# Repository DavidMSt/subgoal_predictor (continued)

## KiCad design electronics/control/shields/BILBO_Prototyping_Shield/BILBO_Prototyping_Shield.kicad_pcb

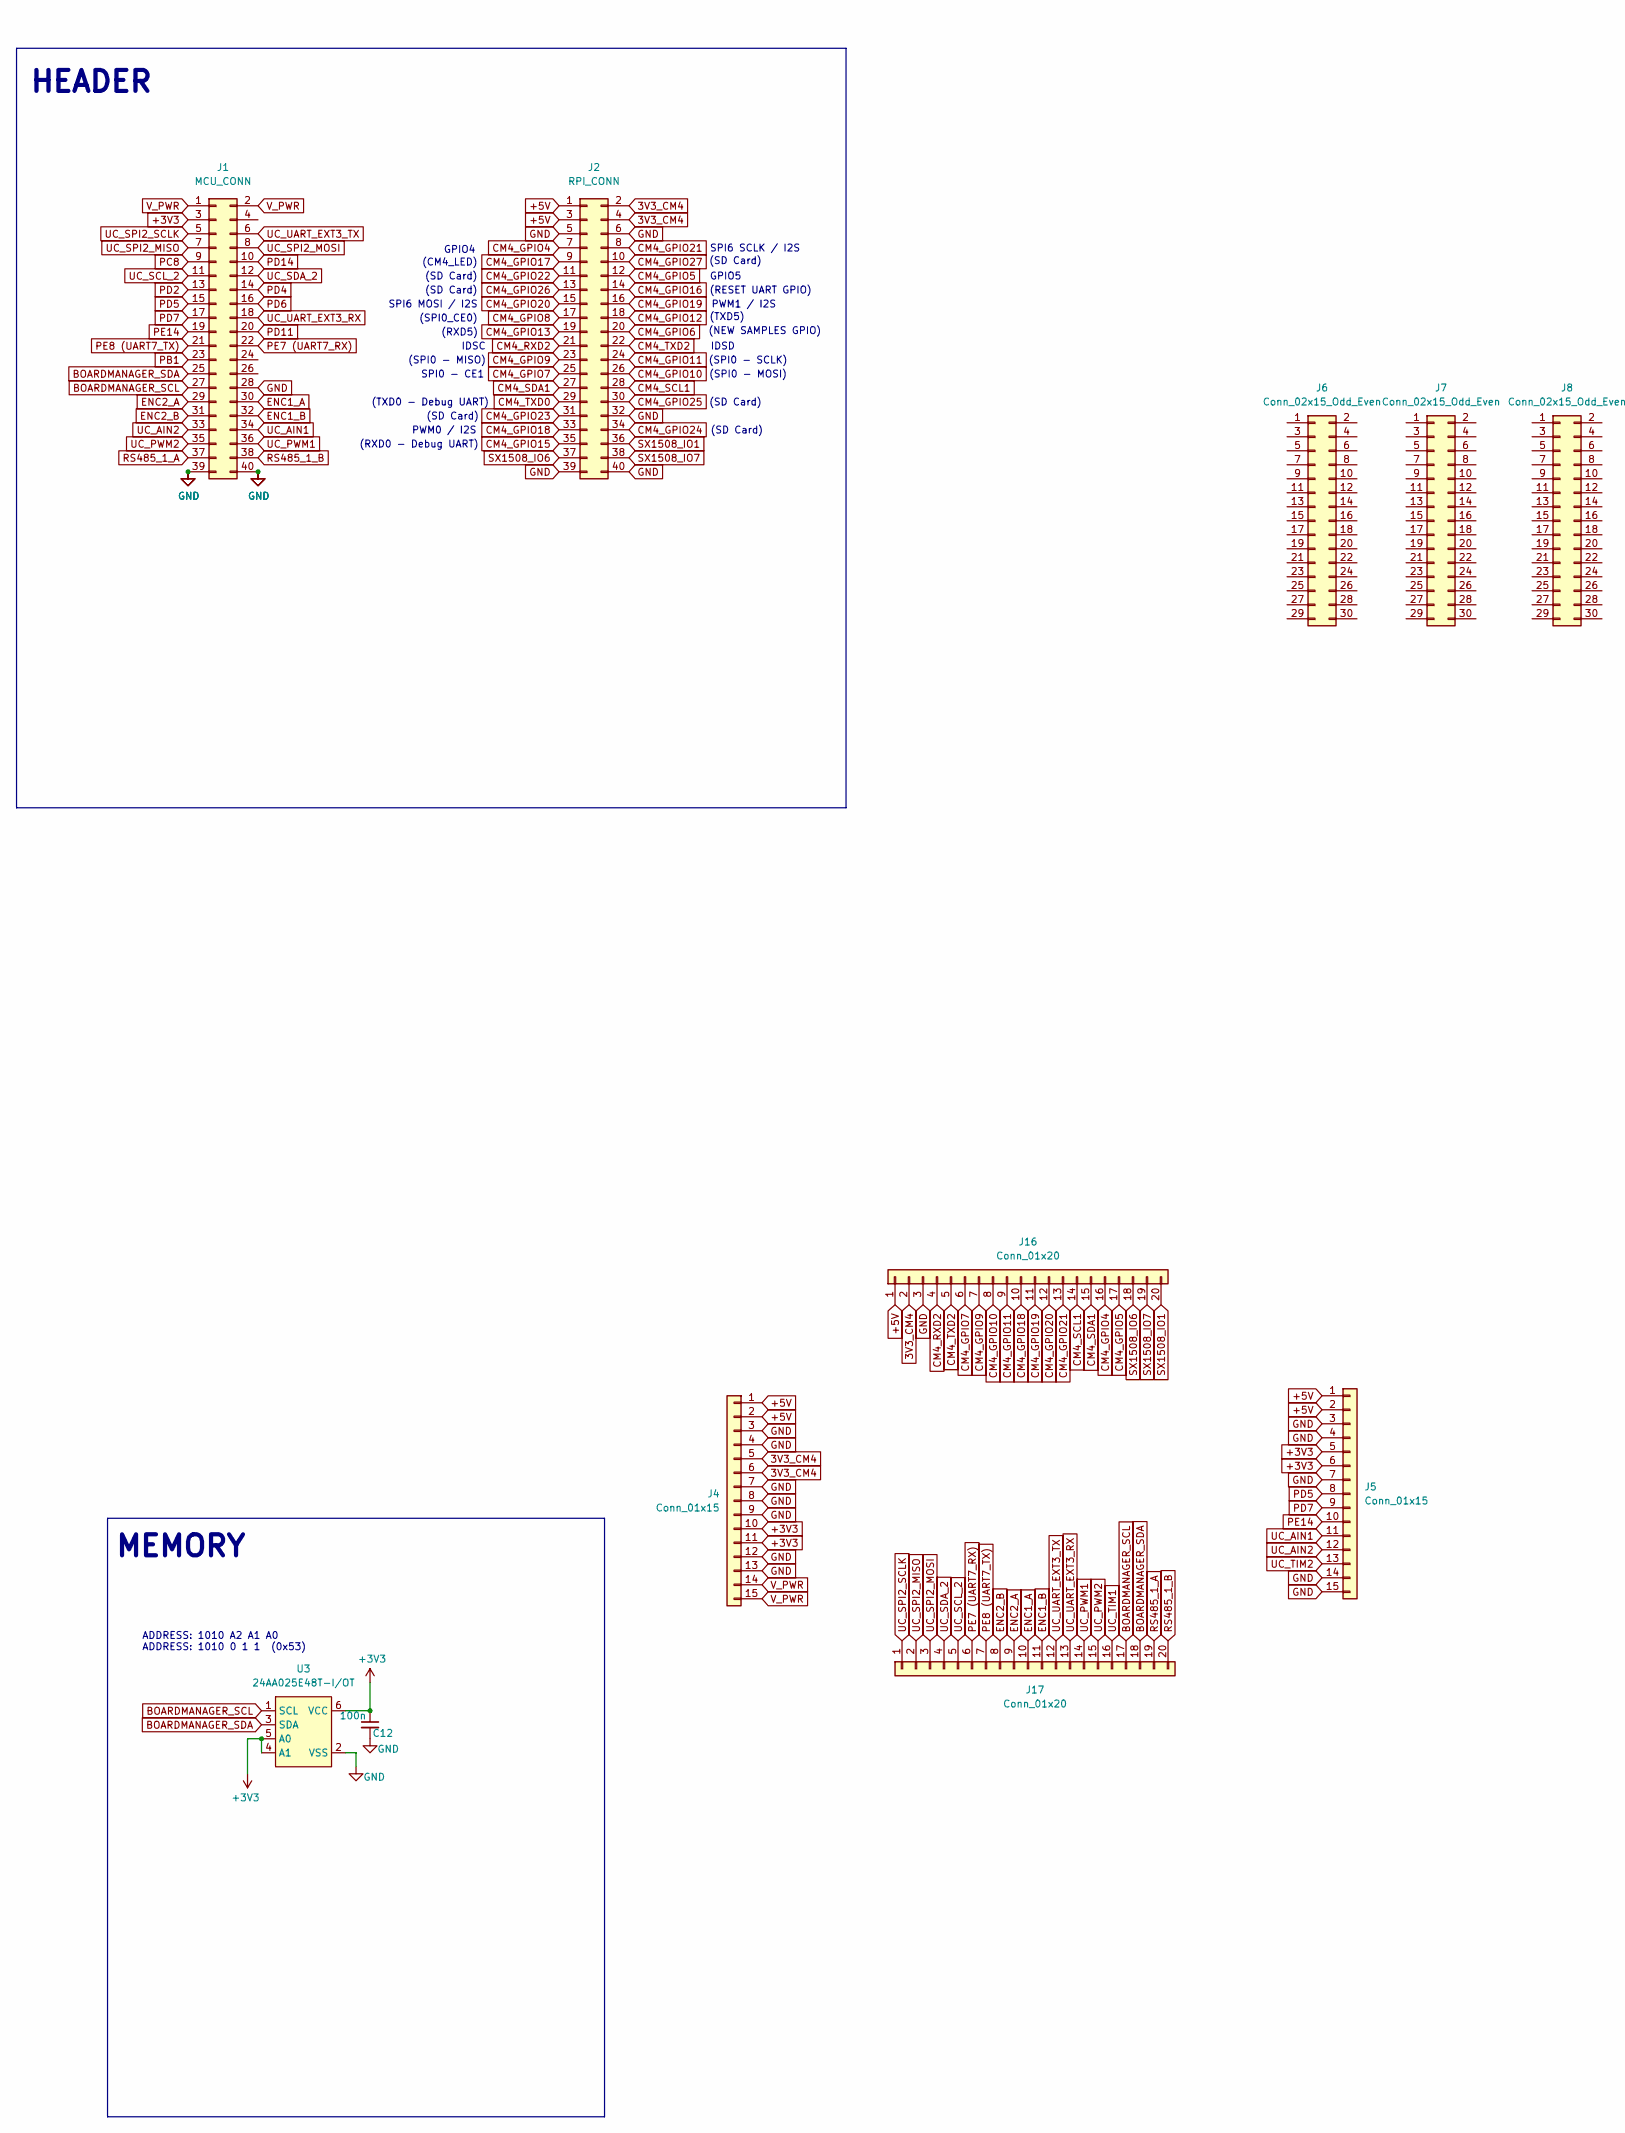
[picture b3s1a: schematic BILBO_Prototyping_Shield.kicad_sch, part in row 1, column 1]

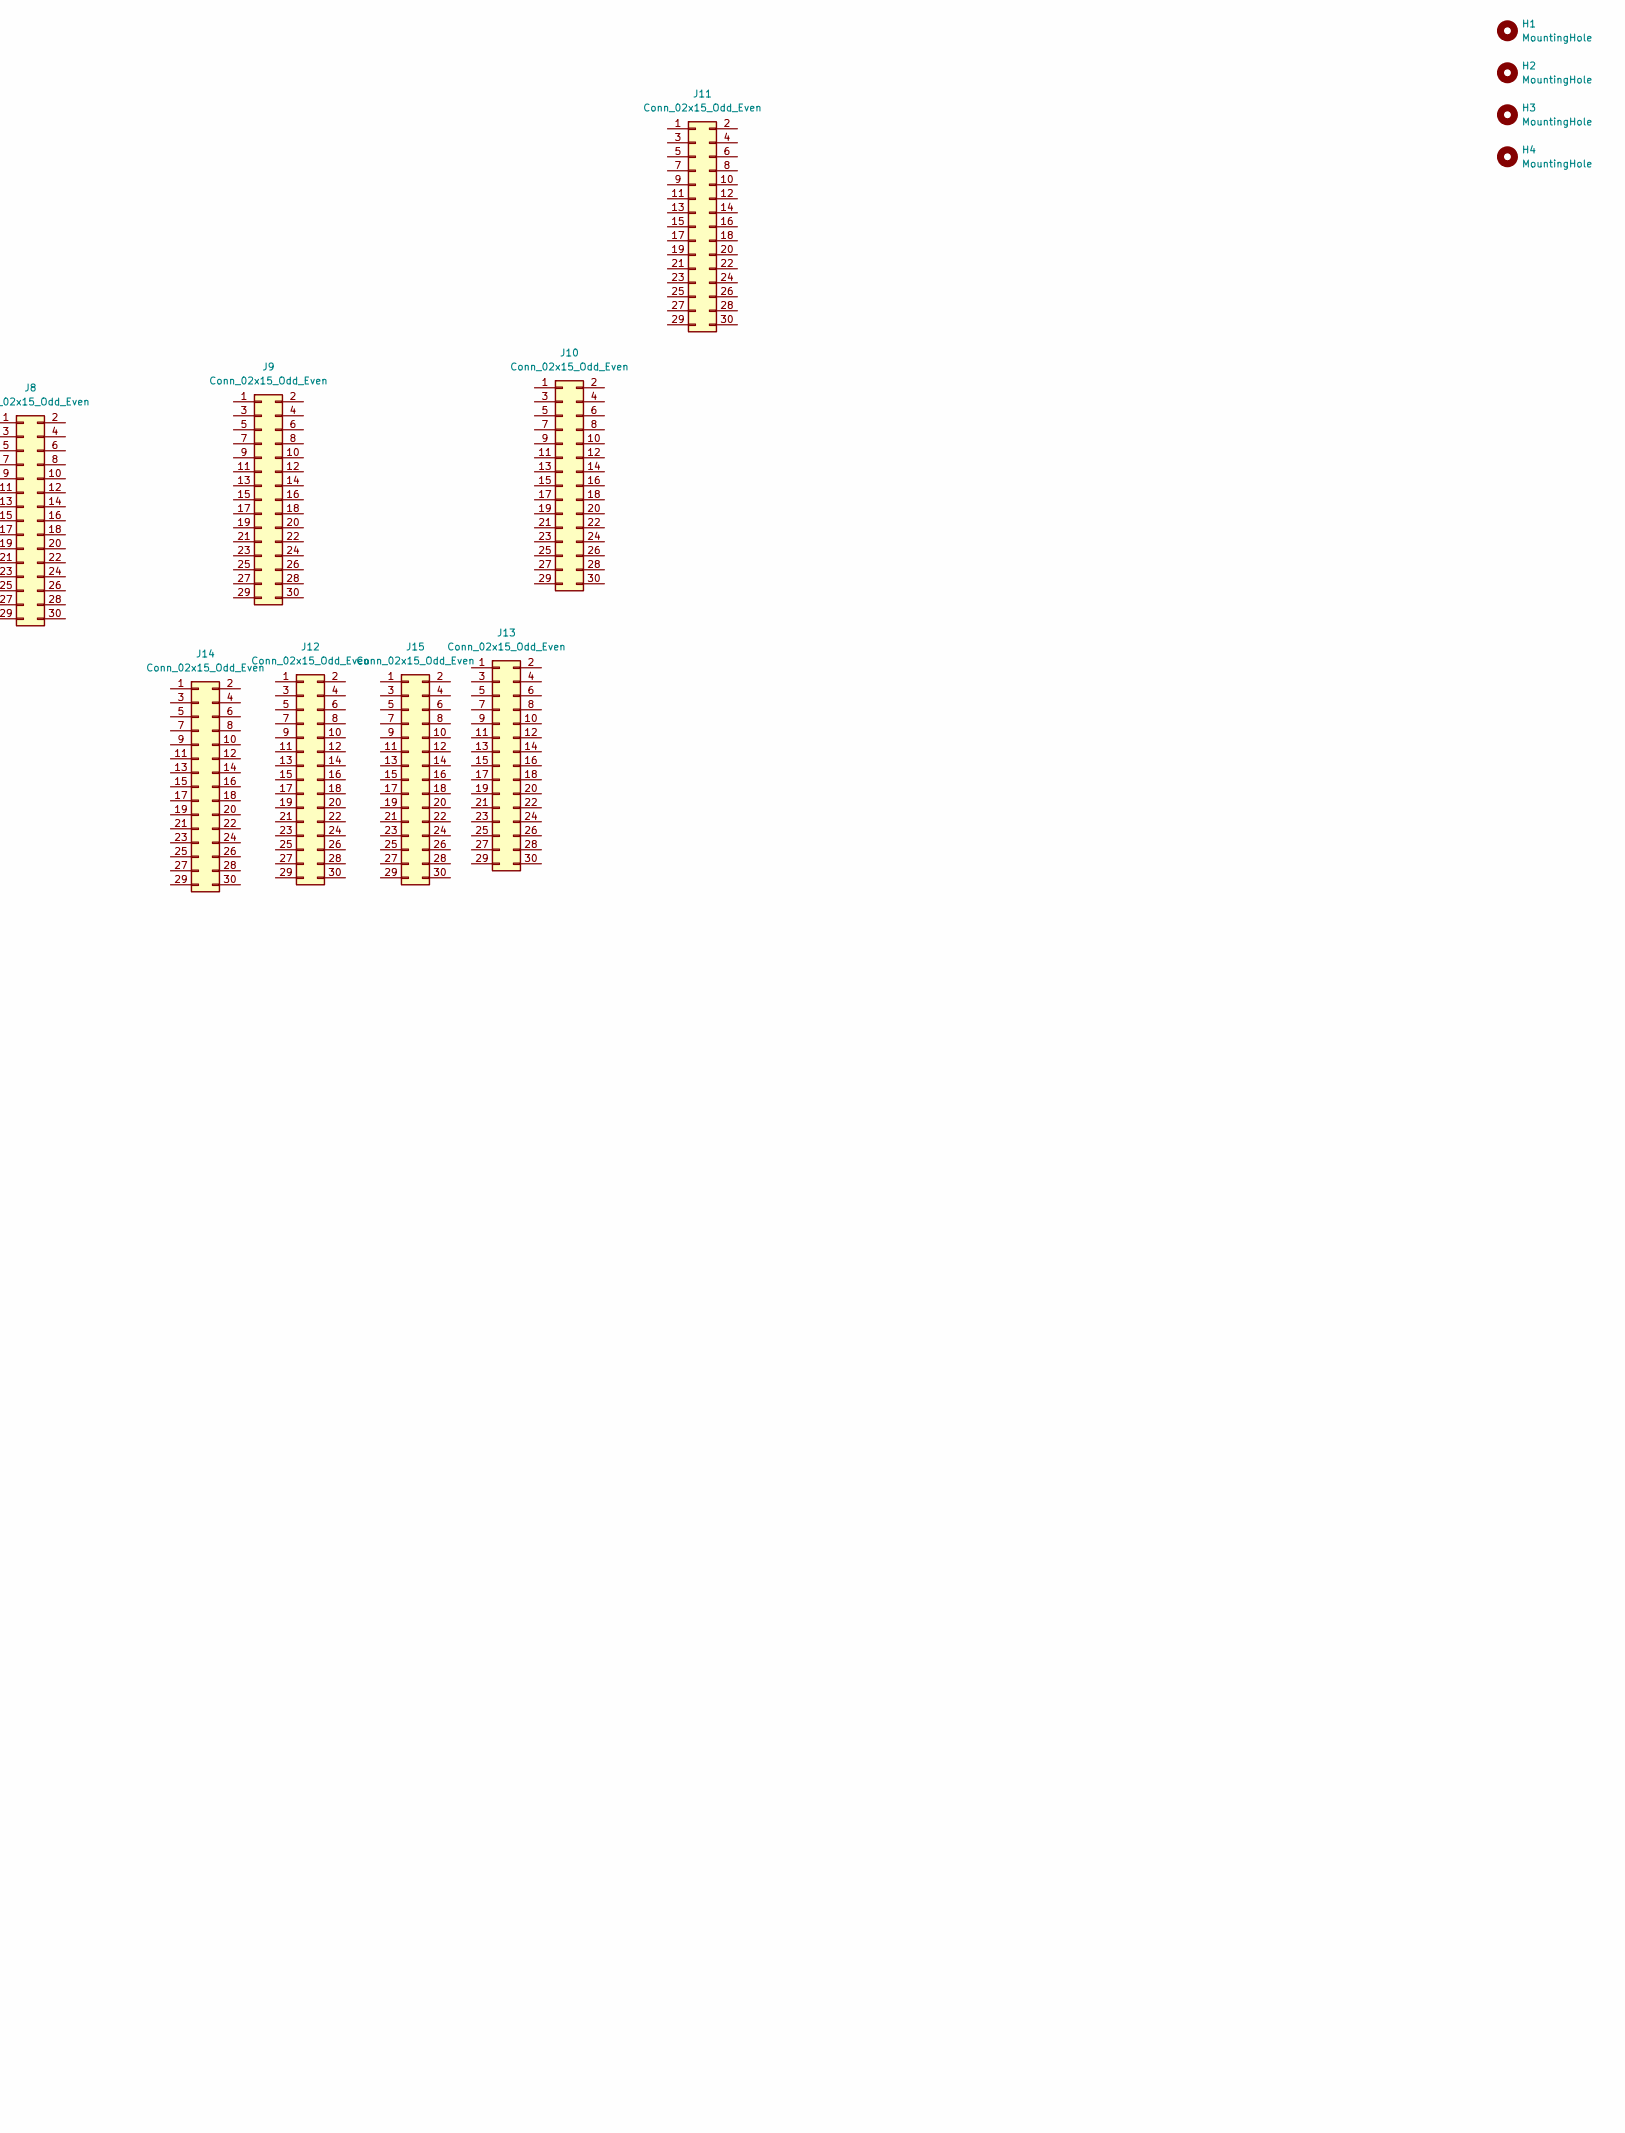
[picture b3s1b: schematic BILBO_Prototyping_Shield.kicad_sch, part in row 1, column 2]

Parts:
C12: 100n; C_0603_1608Metric
H1, H2, H3, H4: MountingHole; MountingHole_2.7mm_M2.5_DIN965
J1: MCU_CONN; PinHeader_2x20_P2.54mm_Vertical
J2: RPI_CONN; PinHeader_2x20_P2.54mm_Vertical
J4, J5: Conn_01x15; PinHeader_1x15_P2.54mm_Vertical
J6, J7, J8, J9, J10, J11, J12, J13, J14, J15: Conn_02x15_Odd_Even; PinHeader_2x15_P2.54mm_Vertical
J16, J17: Conn_01x20; PinHeader_1x20_P2.54mm_Vertical
U3: 24AA025E48T-I/OT; SOT-23-6_Handsoldering

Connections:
3V3_CM4: J2.2, J2.4, J4.5, J4.6, J16.2
+3V3: C12.1, J1.3, J4.10, J4.11, J5.5, J5.6, U3.4 (A1), U3.5 (A0), U3.6 (VCC)
+5V: J2.1, J2.3, J4.1, J4.2, J5.1, J5.2, J16.1
BOARDMANAGER_SCL: J1.27, J17.17, U3.1 (SCL)
BOARDMANAGER_SDA: J1.25, J17.18, U3.3 (SDA)
CM4_GPIO4: J2.7, J16.16
CM4_GPIO5: J2.12, J16.17
CM4_GPIO6: J2.20
CM4_GPIO7: J2.25, J16.6
CM4_GPIO8: J2.17
CM4_GPIO9: J2.23, J16.7
CM4_GPIO10: J2.26, J16.8
CM4_GPIO11: J2.24, J16.9
CM4_GPIO12: J2.18
CM4_GPIO13: J2.19
CM4_GPIO15: J2.35
CM4_GPIO16: J2.14
CM4_GPIO17: J2.9
CM4_GPIO18: J2.33, J16.10
CM4_GPIO19: J2.16, J16.11
CM4_GPIO20: J2.15, J16.12
CM4_GPIO21: J2.8, J16.13
CM4_GPIO22: J2.11
CM4_GPIO23: J2.31
CM4_GPIO24: J2.34
CM4_GPIO25: J2.30
CM4_GPIO26: J2.13
CM4_GPIO27: J2.10
CM4_RXD2: J2.21, J16.4
CM4_SCL1: J2.28, J16.14
CM4_SDA1: J2.27, J16.15
CM4_TXD0: J2.29
CM4_TXD2: J2.22, J16.5
ENC1_A: J1.30, J17.10
ENC1_B: J1.32, J17.11
ENC2_A: J1.29, J17.9
ENC2_B: J1.31, J17.8
GND: C12.2, J1.28, J1.39, J1.40, J2.5, J2.6, J2.32, J2.39, J2.40, J4.3, J4.4, J4.7, J4.8, J4.9, J4.12, J4.13, J5.3, J5.4, J5.7, J5.14, J5.15, J16.3, U3.2 (VSS)
PB1: J1.23
PC8: J1.9
PD2: J1.13
PD4: J1.14
PD5: J1.15, J5.8
PD6: J1.16
PD7: J1.17, J5.9
PD11: J1.20
PD14: J1.10
PE7 (UART7_RX): J1.22, J17.6
PE8 (UART7_TX): J1.21, J17.7
PE14: J1.19, J5.10
RS485_1_A: J1.37, J17.19
RS485_1_B: J1.38, J17.20
SX1508_IO1: J2.36, J16.20
SX1508_IO6: J2.37, J16.18
SX1508_IO7: J2.38, J16.19
UC_AIN1: J1.34, J5.11
UC_AIN2: J1.33, J5.12
UC_PWM1: J1.36, J17.14
UC_PWM2: J1.35, J17.15
UC_SCL_2: J1.11, J17.5
UC_SDA_2: J1.12, J17.4
UC_SPI2_MISO: J1.7, J17.2
UC_SPI2_MOSI: J1.8, J17.3
UC_SPI2_SCLK: J1.5, J17.1
UC_TIM1: J17.16
UC_TIM2: J5.13
UC_UART_EXT3_RX: J1.18, J17.13
UC_UART_EXT3_TX: J1.6, J17.12
V_PWR: J1.1, J1.2, J4.14, J4.15

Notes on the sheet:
(SD Card)
(NEW SAMPLES GPIO)
(TXD0 - Debug UART)
(SPI0 - SCLK)
PWM0 / I2S
(CM4_LED)
ADDRESS: 1010 A2 A1 A0 ADDRESS: 1010 0 1 1 (0x53)
IDSC
(SPI0_CE0)
(RESET UART GPIO)
(SPI0 - MOSI)
MEMORY
SPI6 SCLK / I2S
SPI6 MOSI / I2S
IDSD
GPIO4
(RXD0 - Debug UART)
HEADER
SPI0 - CE1
PWM1 / I2S
(TXD5)
(RXD5)
(SPI0 - MISO)
GPIO5

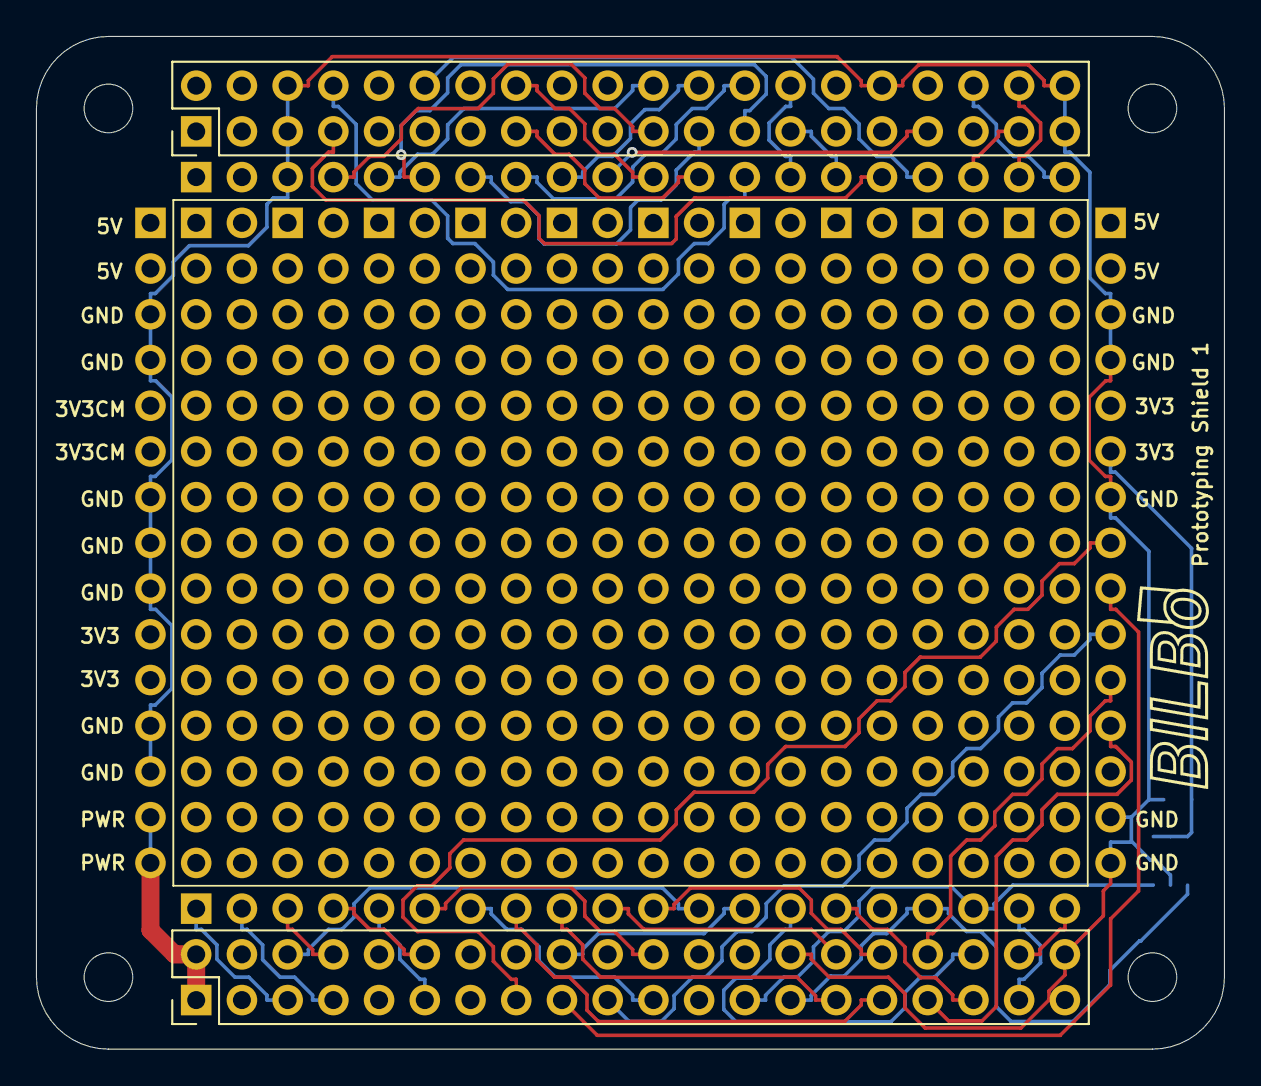
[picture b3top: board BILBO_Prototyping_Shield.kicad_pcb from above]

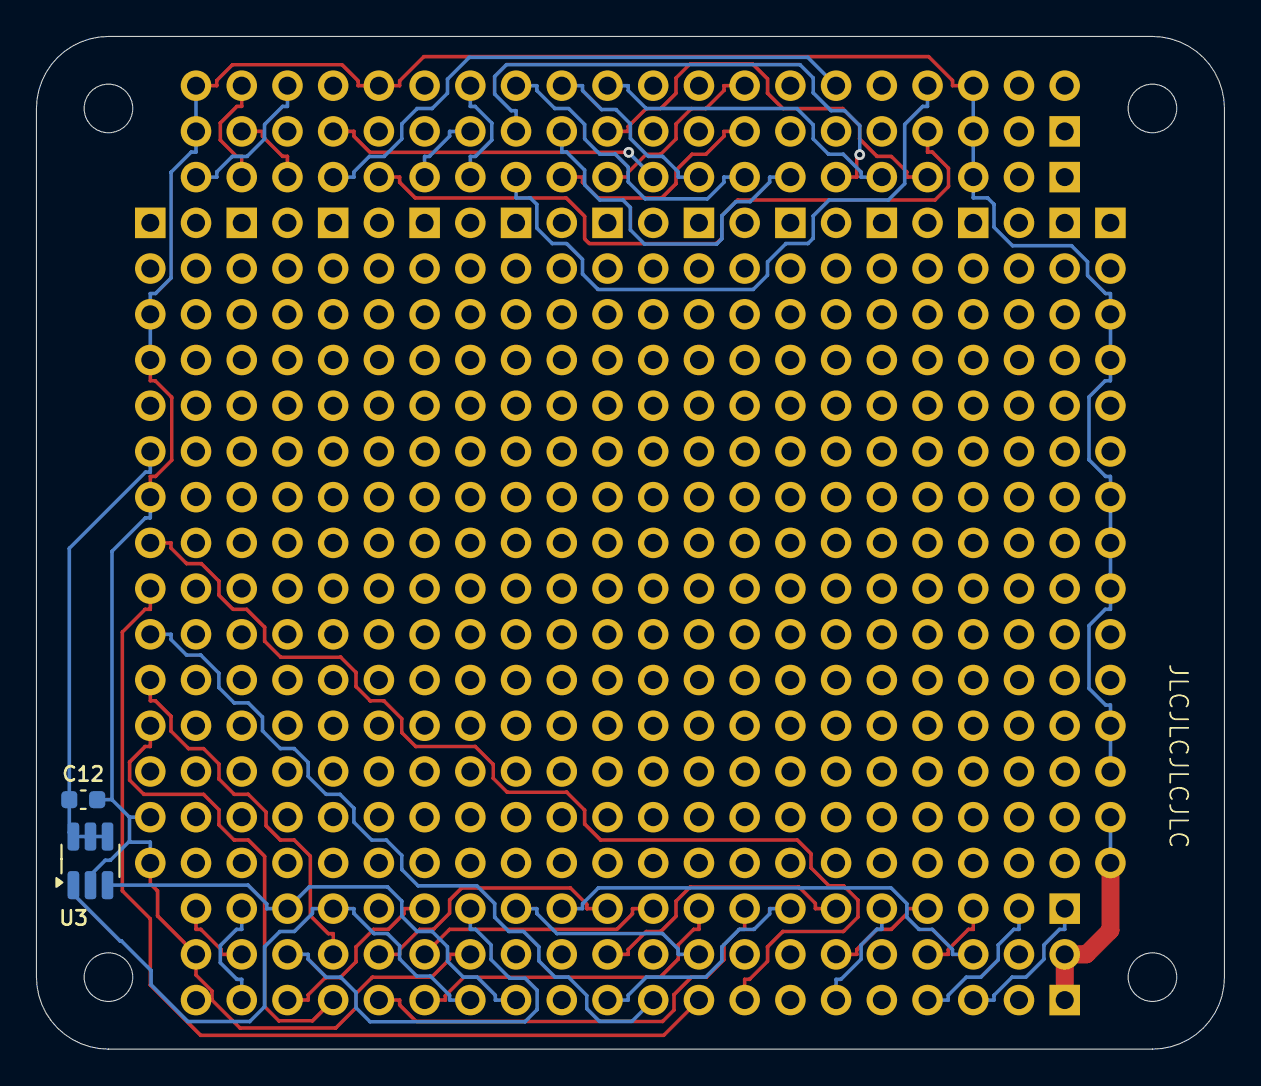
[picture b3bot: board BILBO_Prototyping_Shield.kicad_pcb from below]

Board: 4 copper layers, 66.0 x 56.3 mm, 22 parts (2 on the bottom side), 46 nets.

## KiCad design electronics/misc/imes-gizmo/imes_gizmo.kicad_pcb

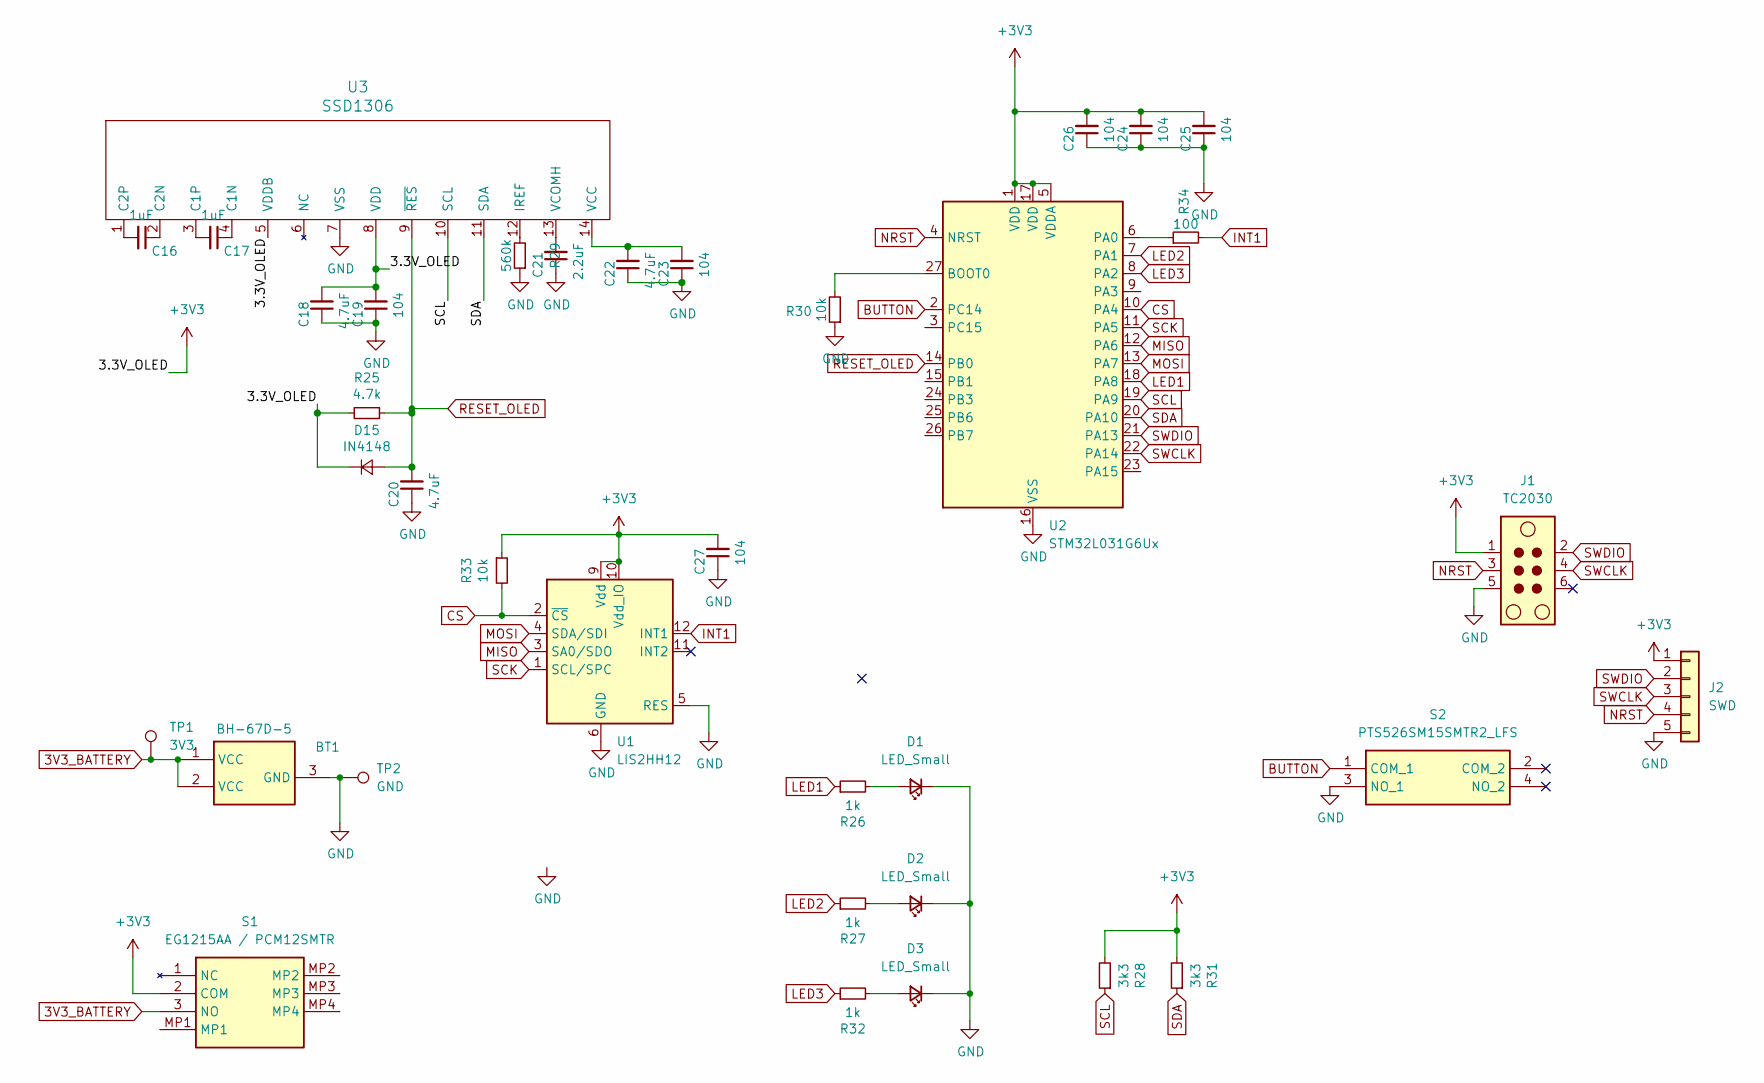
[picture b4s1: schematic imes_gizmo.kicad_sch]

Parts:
BT1: BH-67D-5; BH67D5; Manufacturer_Part_Number BH-67D-5; Mouser Part Number 737-BH-67D-5
C16, C17: 1uF; C_0805_2012Metric
C18, C20, C22: 4.7uF; C_0805_2012Metric
C19, C23, C24, C25, C26, C27: 104; C_0603_1608Metric
C21: 2.2uF; C_0805_2012Metric
D1, D2, D3: LED_Small; LED_0603_1608Metric
D15: IN4148; D_SOD-123
J1: TC2030; Tag-Connect_TC2030-IDC-NL_2x03_P1.27mm_Vertical
J2: SWD; M208900505
R25: 4.7k; R_0603_1608Metric
R26, R27, R32: 1k; R_0603_1608Metric
R28, R31: 3k3; R_0603_1608Metric
R29: 560k; R_0603_1608Metric
R30, R33: 10k; R_0603_1608Metric
R34: 100; R_0603_1608Metric
S1: EG1215AA / PCM12SMTR; EG1215AA; Manufacturer_Part_Number EG1215AA; Mouser Part Number 612-EG1215AA
S2: PTS526SM15SMTR2_LFS; PTS526SM15SMTR2LFS; Manufacturer_Part_Number PTS526SM15SMTR2 LFS; Mouser Part Number 611-PTS526SM15SMTR2L
TP1: 3V3; TestPoint_Pad_D3.0mm
TP2: GND; TestPoint_Pad_D3.0mm
U1: LIS2HH12; LGA-12_2x2mm_P0.5mm
U2: STM32L031G6Ux; QFN50P400X400X60-28N-D
U3: SSD1306; SSD1306_OLED-0.91-128x32

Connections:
3V3_BATTERY: BT1.1 (VCC), BT1.2 (VCC), S1.3 (NO), TP1.1
+3V3: C18.2, C19.2, C24.2, C25.2, C26.2, C27.2, D15.1 (K), J1.1, J2.1, R25.2, R28.2, R31.2, R33.1, S1.2 (COM), U1.9 (Vdd), U1.10 (Vdd_IO), U2.1 (VDD), U2.5 (VDDA), U2.17 (VDD), U3.5 (VDDB), U3.8 (VDD)
BUTTON: S2.1 (COM_1), U2.2 (PC14)
CS: R33.2, U1.2 (~CS), U2.10 (PA4)
GND: BT1.3 (GND), C18.1, C19.1, C20.1, C21.1, C22.1, C23.1, C24.1, C25.1, C26.1, C27.1, D1.1 (K), D2.1 (K), D3.1 (K), J1.5, J2.5, R29.1, R30.1, S2.3 (NO_1), TP2.1, U1.5 (RES), U1.6 (GND), U1.7 (GND), U1.8 (GND), U2.16 (VSS), U2.28 (VSS), U3.7 (VSS)
INT1: R34.2, U1.12 (INT1)
LED1: R26.1, U2.18 (PA8)
LED2: R27.1, U2.7 (PA1)
LED3: R32.1, U2.8 (PA2)
MISO: U1.3 (SA0/SDO), U2.12 (PA6)
MOSI: U1.4 (SDA/SDI), U2.13 (PA7)
NRST: J1.3, J2.4, U2.4 (NRST)
unnamed: D1.2 (A), R26.2
unnamed: D2.2 (A), R27.2
unnamed: D3.2 (A), R32.2
unnamed: R30.2, U2.27 (BOOT0)
unnamed: R34.1, U2.6 (PA0)
unnamed: C17.1, U3.4 (C1N)
unnamed: C17.2, U3.3 (C1P)
unnamed: C16.1, U3.2 (C2N)
unnamed: C16.2, U3.1 (C2P)
unnamed: R29.2, U3.12 (IREF)
unnamed: C22.2, C23.2, U3.14 (VCC)
unnamed: C21.2, U3.13 (VCOMH)
RESET_OLED: C20.2, D15.2 (A), R25.1, U2.14 (PB0), U3.9 (~RES)
SCK: U1.1 (SCL/SPC), U2.11 (PA5)
SCL: R28.1, U2.19 (PA9), U3.10 (SCL)
SDA: R31.1, U2.20 (PA10), U3.11 (SDA)
SWCLK: J1.4, J2.3, U2.22 (PA14)
SWDIO: J1.2, J2.2, U2.21 (PA13)

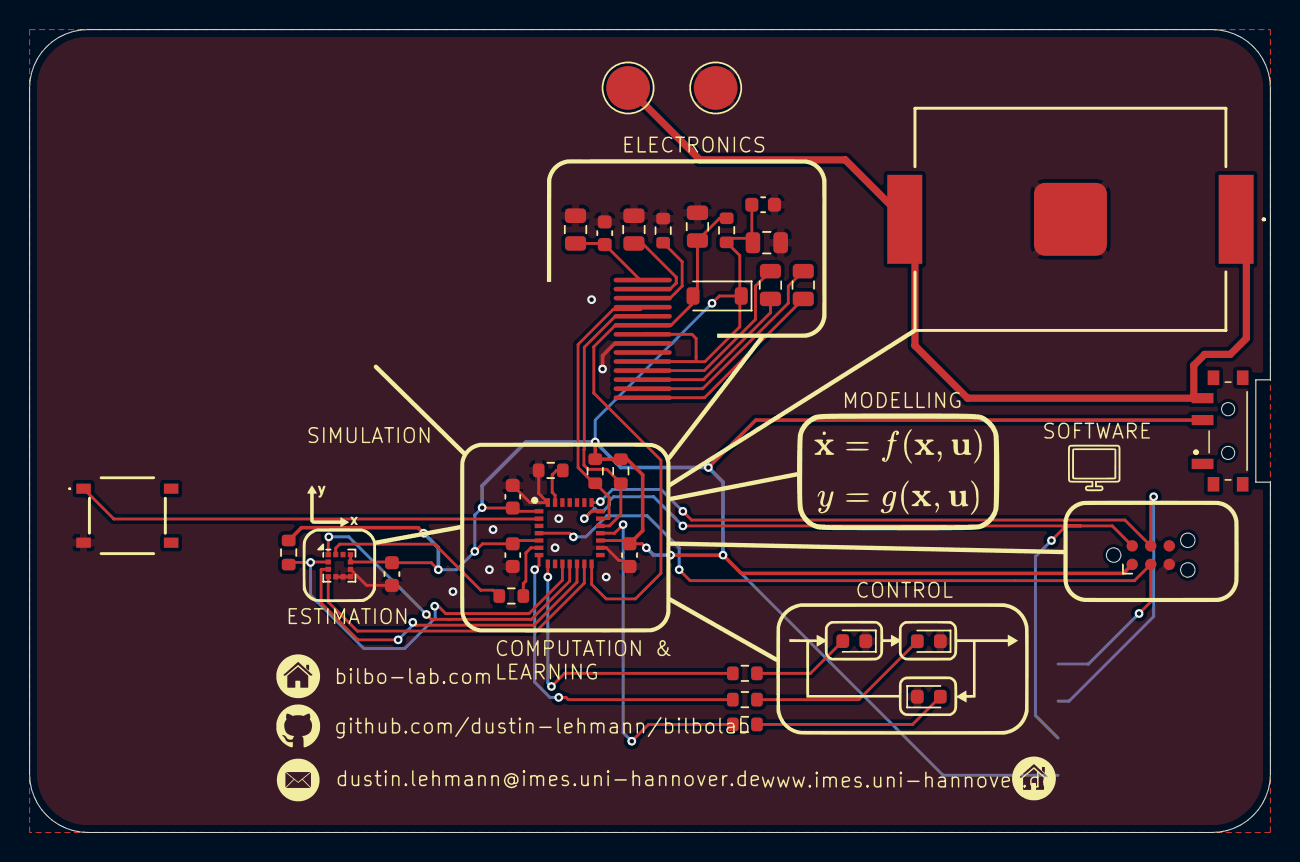
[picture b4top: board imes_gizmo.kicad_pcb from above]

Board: 2 copper layers, 85.0 x 55.0 mm, 36 parts (1 on the bottom side), 30 nets.

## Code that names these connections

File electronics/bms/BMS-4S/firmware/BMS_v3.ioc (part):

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Mcu.Name=STM32L432K(B-C)Ux
Mcu.Package=UFQFPN32
Mcu.UserName=STM32L432KBUx
PA0.Signal=ADCx_IN5
PA1.GPIOParameters=GPIO_Label
PA1.GPIO_Label=ENABLE_MEAS_1
PA1.Signal=GPIO_Output
PA10.Mode=I2C
PA10.Signal=I2C1_SDA
PA11.GPIOParameters=GPIO_Label
PA11.GPIO_Label=LED_USER
PA11.Signal=GPIO_Output
PA13\ (JTMS-SWDIO).Mode=Serial_Wire
PA13\ (JTMS-SWDIO).Signal=SYS_JTMS-SWDIO
PA14\ (JTCK-SWCLK).Mode=Serial_Wire
PA14\ (JTCK-SWCLK).Signal=SYS_JTCK-SWCLK
PA15\ (JTDI).Signal=GPIO_Analog
PA2.Signal=ADCx_IN7
PA4.Signal=ADCx_IN9
PA5.GPIOParameters=GPIO_Label
PA5.GPIO_Label=ENABLE_MEAS_3
PA5.Signal=GPIO_Output
PA6.GPIOParameters=GPIO_PuPd,GPIO_Label
PA6.GPIO_Label=DETECT_CHG
PA6.GPIO_PuPd=GPIO_PULLUP
PA6.Signal=GPIO_Input
PA7.Mode=I2C
PA7.Signal=I2C3_SCL
PA9.Mode=I2C
PA9.Signal=I2C1_SCL
PB0.Signal=ADCx_IN15
PB1.GPIOParameters=GPIO_Label
PB1.GPIO_Label=ENABLE_MEAS_4
PB1.Signal=GPIO_Output
PB3\ (JTDO-TRACESWO).GPIOParameters=GPIO_Label
PB3\ (JTDO-TRACESWO).GPIO_Label=OUT_2
PB3\ (JTDO-TRACESWO).Signal=GPIO_Output
PB4\ (NJTRST).Mode=I2C
PB4\ (NJTRST).Signal=I2C3_SDA
PB5.GPIOParameters=GPIO_Label
PB5.GPIO_Label=OUT_1
PB5.Signal=GPIO_Output
PB6.GPIOParameters=GPIO_Label
PB6.GPIO_Label=OUT_3
PB6.Signal=GPIO_Output
PB7.GPIOParameters=GPIO_Label
PB7.GPIO_Label=OUT_4
PB7.Signal=GPIO_Output
RCC.HSE_VALUE=8000000
RCC.SYSCLKFreq_VALUE=16000000
RCC.SYSCLKSource=RCC_SYSCLKSOURCE_HSI
board=custom

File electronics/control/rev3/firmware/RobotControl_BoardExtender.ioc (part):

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Mcu.Name=STM32G031G(4-6-8)Ux
Mcu.Package=UFQFPN28
Mcu.UserName=STM32G031G8Ux
PA0.Mode=IN0
PA0.Signal=ADC1_IN0
PA1.Mode=IN1
PA1.Signal=ADC1_IN1
PA11\ [PA9].Mode=I2C
PA11\ [PA9].Signal=I2C2_SCL
PA12\ [PA10].Mode=I2C
PA12\ [PA10].Signal=I2C2_SDA
PA13.Mode=Serial_Wire
PA13.Signal=SYS_SWDIO
PA14-BOOT0.Mode=Serial_Wire
PA14-BOOT0.Signal=SYS_SWCLK
PA15.GPIOParameters=GPIO_Label
PA15.GPIO_Label=LED
PA15.Signal=GPIO_Output
PA2.GPIOParameters=GPIO_Label
PA2.GPIO_Label=ENABLE_SD
PA2.Signal=GPIO_Output
PA3.Mode=IN3
PA3.Signal=ADC1_IN3
PA4.GPIOParameters=GPIO_Label
PA4.GPIO_Label=DETECT_SD
PA4.Signal=GPIO_Input
PA5.GPIOParameters=GPIO_PuPd
PA5.GPIO_PuPd=GPIO_PULLDOWN
PA5.Signal=S_TIM2_CH1_ETR
PA6.GPIOParameters=GPIO_PuPd,GPIO_Label
PA6.GPIO_Label=DETECT_USB
PA6.GPIO_PuPd=GPIO_PULLUP
PA6.Signal=GPIO_Input
PA8.GPIOParameters=GPIO_Label
PA8.GPIO_Label=DEBUG_JMP
PA8.Signal=GPIO_Input
PB0.GPIOParameters=GPIO_Label
PB0.GPIO_Label=LED_USB
PB0.Signal=GPIO_Output
PB1.GPIOParameters=GPIO_Label
PB1.GPIO_Label=BUTTON_EXT
PB1.Signal=GPIO_Input
PB3.Signal=S_TIM1_CH2
PB4.Signal=S_TIM3_CH1
PB5.GPIOParameters=GPIO_Label
PB5.GPIO_Label=ENABLE_5V
PB5.Signal=GPIO_Output
PB6.Mode=I2C
PB6.Signal=I2C1_SCL
PB7.Mode=I2C
PB7.Signal=I2C1_SDA
PB8.GPIOParameters=GPIO_Label
PB8.GPIO_Label=CM4_3V3
PB8.Signal=GPIO_Input
PC6.GPIOParameters=GPIO_PuPd,GPIO_Label
PC6.GPIO_Label=ENABLE_CM4
PC6.GPIO_PuPd=GPIO_PULLDOWN
PC6.Signal=GPIO_Output
RCC.HSE_VALUE=8000000
RCC.SYSCLKFreq_VALUE=64000000
RCC.SYSCLKSource=RCC_SYSCLKSOURCE_PLLCLK
board=custom

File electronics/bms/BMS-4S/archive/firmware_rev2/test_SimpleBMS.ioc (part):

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Mcu.Name=STM32L432K(B-C)Ux
Mcu.Package=UFQFPN32
Mcu.UserName=STM32L432KBUx
PA1.GPIOParameters=GPIO_Label
PA1.GPIO_Label=ENABLE_MEAS_1
PA1.Signal=GPIO_Output
PA11.GPIOParameters=GPIO_Label
PA11.GPIO_Label=LED_USER
PA11.Signal=GPIO_Output
PA12.GPIOParameters=GPIO_Label
PA12.GPIO_Label=LED_POWER
PA12.Signal=GPIO_Output
PA13\ (JTMS-SWDIO).Mode=Serial_Wire
PA13\ (JTMS-SWDIO).Signal=SYS_JTMS-SWDIO
PA14\ (JTCK-SWCLK).Mode=Serial_Wire
PA14\ (JTCK-SWCLK).Signal=SYS_JTCK-SWCLK
PA15\ (JTDI).Signal=GPIO_Analog
PA4.GPIOParameters=GPIO_Label
PA4.GPIO_Label=ADC_CELL_3
PA4.Signal=ADCx_IN9
PA5.GPIOParameters=GPIO_Label
PA5.GPIO_Label=ENABLE_MEAS_3
PA5.Signal=GPIO_Output
PA8.GPIOParameters=GPIO_Label
PA8.GPIO_Label=LED_LOW
PA8.Signal=GPIO_Output
PB0.GPIOParameters=GPIO_Label
PB0.GPIO_Label=ADC_CELL_4
PB0.Signal=ADCx_IN15
PB1.GPIOParameters=GPIO_Label
PB1.GPIO_Label=ENABLE_MEAS_4
PB1.Signal=GPIO_Output
PB3\ (JTDO-TRACESWO).GPIOParameters=GPIO_Label
PB3\ (JTDO-TRACESWO).GPIO_Label=OUT_2
PB3\ (JTDO-TRACESWO).Signal=GPIO_Output
PB5.GPIOParameters=GPIO_Label
PB5.GPIO_Label=OUT_1
PB5.Signal=GPIO_Output
PB6.GPIOParameters=GPIO_Label
PB6.GPIO_Label=OUT_3
PB6.Signal=GPIO_Output
RCC.HSE_VALUE=8000000
RCC.SYSCLKFreq_VALUE=16000000
RCC.SYSCLKSource=RCC_SYSCLKSOURCE_HSI
board=custom

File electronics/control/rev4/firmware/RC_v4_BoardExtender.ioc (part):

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Mcu.Name=STM32L431C(B-C)Ux
Mcu.Package=UFQFPN48
Mcu.UserName=STM32L431CCUx
PA0.Signal=S_TIM2_CH1
PA10.Mode=I2C
PA10.Signal=I2C1_SDA
PA12.GPIOParameters=GPIO_Label
PA12.GPIO_Label=USER_BUTTON_ON_BOARD
PA12.Signal=GPIO_Input
PA13\ (JTMS-SWDIO).Mode=Serial_Wire
PA13\ (JTMS-SWDIO).Signal=SYS_JTMS-SWDIO
PA14\ (JTCK-SWCLK).Mode=Serial_Wire
PA14\ (JTCK-SWCLK).Signal=SYS_JTCK-SWCLK
PA15\ (JTDI).GPIOParameters=GPIO_Label
PA15\ (JTDI).GPIO_Label=LED_STATUS
PA15\ (JTDI).Signal=GPIO_Output
PA2.Signal=S_TIM15_CH1
PA3.Signal=ADCx_IN8
PA8.Signal=S_TIM1_CH1
PA9.Mode=I2C
PA9.Signal=I2C1_SCL
PB10.Mode=I2C
PB10.Signal=I2C2_SCL
PB11.Mode=I2C
PB11.Signal=I2C2_SDA
PB12.GPIOParameters=GPIO_Label
PB12.GPIO_Label=SD_CARD_SWITCH
PB12.Signal=GPIO_Input
PB13.GPIOParameters=GPIO_Label
PB13.GPIO_Label=ENABLE_SD
PB13.Signal=GPIO_Output
PB2.GPIOParameters=GPIO_Label
PB2.GPIO_Label=USER_BUTTON_1
PB2.Signal=GPIO_Input
PB3\ (JTDO-TRACESWO).GPIOParameters=GPIO_Label
PB3\ (JTDO-TRACESWO).GPIO_Label=LED_ERROR
PB3\ (JTDO-TRACESWO).Signal=GPIO_Output
PB6.GPIOParameters=GPIO_Label
PB6.GPIO_Label=ENABLE_CM4
PB6.Signal=GPIO_Output
RCC.HSE_VALUE=8000000
RCC.SYSCLKFreq_VALUE=32000000
RCC.SYSCLKSource=RCC_SYSCLKSOURCE_PLLCLK
board=custom

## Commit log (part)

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2025-11-24 updated universal simulation class
2025-11-24 cosmetics
2025-11-24 start of clean-up and adjusting task assignment to work with new structure
2025-11-24 added pid control to WS25/26 project group folder
2025-11-24 added new colorways for predefined frodo list
2025-11-25 began implementation of geometric planner with splines for FRODO
2025-11-25 added opt base file from lecture exercise which now has to be adjusted to work with frodo and without yaml files
2025-11-26 instead of creating the agent collision manager anew for each check, it now only updates the agent config for each state to be tested which should reduce overhead significantly
2025-11-26 cosmetics and introduction of new demo file which will be used to demo the individual capabilities of the software
2025-11-26 Bugfixes in BILBO Software
2025-11-26 further improved container structure, now also added a local world representation which can be used to store and exchange containers in a truly decentralized manner.
2025-11-26 integrated the world representation into frodo state
2025-11-27 adjusting the new agent method to the new architecture with containers, also minor cosmetics
2025-11-27 moved the command set to universal agent, since this will implement all the stuff
2025-11-28 added the creation and update for environment containers
2025-12-02 fixed minor initialization bugs, obstacle now directly inherit from object, also their output function is now just a dummy
2025-12-02 fixed teh container update function, simulation appears to run for the first time since remodeling with containers
2025-12-02 improved printouts, added new test in the general simulation main-function
2025-12-02 added overarching motion planning container similar to agent and envrionment ones
2025-12-02 updated motion planning pipeline to container-use
2025-12-02 fixed example scenario
2025-12-03 simple maze button works now
2025-12-03 renamed mp containers for better clarity of purpose
2025-12-03 renamed containers for clarity, adjusted task assignment container
2025-12-03 update for tasks
2025-12-03 - fixed import path errors - added tasks to general_simulation such that task assignment interface only has to do assignment related things
2025-12-03 renaming for clarity
2025-12-04 added an occupancy grid to the environment which should help spawning tasks/ agents and also might be useful for passing an agent observations during RL
2025-12-04 adding objects (tasks, agents, obstacles) now updates the occupancy grids, object creation now frozen after simulation started to ease the use of
2025-12-04 added button to spawn both agents and tasks (because of one-to-one assignment)
2025-12-05 fixed Assignment agent to work with refactored module
2025-12-05 created separate file for General Environment
2025-12-05 moved tasks to general, rename them accordingly
2025-12-05 removed statics dict in the simulatoin since those are obstacles and tasks in my case
2025-12-05 major refactor to integrate ta containers better - now no need to pass actual instances of agents/tasks, asignment interface works only with containers, publishes new states in case of decentral plan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
2025-12-06 created function header for autnomoous handling of task assignment/ motion planning
2025-12-06 added default values for container, created execution container dummy and adjusted universal agent class
2025-12-06 focusing on the central assignment implementation now, therefore only stumps implemented for decentral
2025-12-08 Update readme with project and contribution details
    Expanded the readme to include project overview and contribution details.
2025-12-08 Update README with running instructions
    Added instructions for running the project.
2025-12-08 Revise contribution overview list formatting
    Updated the contribution overview list format for clarity.
2025-12-09 small requirements.txt update
2025-12-09 moved and ajdusted the context class to a proper container
2025-12-09 fixed wrong type assumption for containers
2025-12-09 small bugfix
2025-12-09 updating dataset generation for the new method
2025-12-09 changed the mp pipepline to exclusively work with containers now. Usage of the same motion planner instance now for multiple runs, reducing overhead when needed to create anew each time . Also some c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
2025-12-09 added check, if objects are within specified envrionment limits
2025-12-10 introduced separate containers for simulation and agent ta (latter used additionally for local decisions in decentral assignments)
2025-12-10 BUGFIX: obstacle modified the environment limits upon creation, now removed
2025-12-10 renaming container files
2025-12-10 began working on local environment container
2025-12-10 introduction of the local world representation of an agent + update from the env added
2025-12-10 modified decetnralized ta_strategies to return predicted task, allowing per agent execution
2025-12-10 made the default for decentralized strategies multi-round to easier break conflicts later
2025-12-11 cosmetics for better clarity, ongoing implementation of central TA
2025-12-11 centralized assginments now returns agent - task ids from assignment
2025-12-12 centralized methods now write the task into the agents ta container
2025-12-12 removed by introduction of lwr redundant functions in tai
2025-12-12 adjusted the mp sim module to work with containers exclusively
2025-12-12 fixed logging bug, when setter value is None, minor cosmetics
2025-12-12 bug of empty mp agent containers of simulation fixed, added dummi execution agent module + container
2025-12-14 added execution capabilities that were missing, restructured mp container
2025-12-14 cosmetecis done, ompl now returns seconds instead of timesteps
2025-12-15 fixed bug during execution which lead to sim Ts differ from agent Ts, causing the steps per phase to be off by a factor of 10
2025-12-15 adjusted max duration of kinodynamic rrt to always equal one second. Improves planner performance significantly!
2025-12-15 new 2x2 maze, started with the 4x4 version
2025-12-25 improved decentralized ta
2025-12-25 first steps in refactoring ta agent module for local ta
2025-12-26 decentralized ta fully functional
2025-12-26 moved individual modules into dedicated modules folder
2025-12-26 minor cosmetics
2025-12-26 motion planning module now uses the lwr container instead of an environment container
2026-01-05 started adding the gym wrapper
2026-01-07 Bugfixes
2026-01-08 removed training logs from git tracking
2026-01-08 made rl episode output much cleaner
2026-01-19 moved gnn files into subfolder, implemented dgnn-ga more accurately - not functional yet
2026-01-20 added file for cost computation, fixed bug with thidden dim of the encoder
2026-01-20 added communication density for training and validation in hopes to combat embedding collapse during first decoder
2026-01-29 updated dataset creation to cost as input. moved dataset functions into train utils as well
2026-02-03 added validation loop
2026-02-04 updated training loop in test
2026-02-06 Removed test command in the bilbo application
2026-02-06 refactored gnn training, updated loss computation, model reached f1 ~0.9
2026-02-09 cosmetics, started implementation of dgnnga as assignment strategy
2026-02-10 mergedd both planner agent classes and re-renamed it to universal agent, fixed cost computation for individual agents
2026-02-10 fixed visible neighbors by excluding agent itself, fixed waiting for communication method during TA
2026-02-11 Updated Optitrack
2026-02-11 Bugfix in keepalive
2026-02-12 implemented decentralized communication mechanism, but true parallel exeuction needed to process further
2026-02-12 cosmetics related to dgnn-ga
2026-02-14 Removed test file
2026-02-16 added GUI support for all agent types with trajectory visualization
    - Python wrappers for Babylon CircleDrawing and LineDrawing
    - Type-specific spawn buttons (Offline blue, Reactive green)
    - Assignment circles colored by task, following agents in real-time
    - Trajectory visualization: OMPL waypoints (solid), reactive subgoals
    (dashed), RL subgoal→goal (dotted)
    - One-click "Run Pipeline" button (TA → MP → EXE)
2026-02-23 removed unnecessary readme
2026-03-02 add subgoal NN, gym wrapper improvements, and REINFORCE training stub
    - subgoal_nn_base: per-modality encoders (agent, neighbors, goal,
    neighbor_goals, CNN grid encoder) + regression head for n_subgoals
    - FrodoGymWrapper: n_subgoals param, goal_states/neighbor_goals obs,
    _assign_subgoals(), start_ta/mp/exe() pipeline in reset/step
    - train(): REINFORCE loop with Gaussian exploration and reward normalization
    - TODO: grid_resolution 10cm → 1cm upgrade with pooling before flatten
2026-03-09 added PRM*, for precomputing roadmap once and reusing it during RL, after collision fall back to splined-rrt version
2026-03-09 removed containers from motion planning directly, to have it being independent from them - added test case. Cleaned up the OMPL planner file, removed unnecessary base class, since kinodyn-rrt has bee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
2026-03-10 cosmetics (added comments)
2026-03-10 removed redundant and outdated rl files
2026-03-10 rdp in rare cases did lead to cutting away points going around edges (RRT case) leading to paths in collision with obstacles, therefore rdp is temporarily removed, for better debugging start and end 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
2026-03-11 implemented spawn regions for tasks and agents, can be used on new_agent() call and already in the scenario definition. To make placement more area-efficient (placing more in tighter space) we now mo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
2026-03-11 added nudging to ompl, slightly modify start position when we are in collision to enable motion planning out of collisions. Enabled collision detection agent-obstacle, by using the agents collision c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
2026-03-13 removed outdated/ duplicated files
2026-03-13 added README to the master thesis folder
2026-03-13 no scenarios only in yaml format, adjusted code to only handle those cases no python files anymore
2026-03-16 gui now uses the last rl-trainig results by default. Added more args to the training file, modifications in-between runs more easy now.
2026-03-20 added new scenarios for rl, further simplification of the first training scenario (limited action space, scenario now fixed no random spawning of tasks and agents, ...)
2026-04-01 changed reward structure, switched to GNN subgoal prediction, fixed broken PRM* pipeline, not only RRT* used as a result.
2026-04-17 now prm used always for intial plan. Added new training scenarios, modified existing ones
2026-04-21 safecopy for weights and trainig documentation
2026-04-30 thesis submission update.
2026-04-30 Update thesis README files
2026-05-27 moved subgoal nn architectures into dedicated file. Lot of cosmetics. Changes made to the bipartite GNN: Added space encoder for distance to walls of testbed; Added continuous prediction head for pos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
2026-05-31 cosmetics, improved code structure: Now three RL run modes, evaluate,resume, train
2026-06-06 continuous prediction space adjusted - in remaining files - no backward compatibility implemented since new approach should be single sourrc of truth.
2026-06-14 switched requirements for pyproject.toml
2026-06-21 add replan_block_s: freeze agent after collision-recovery replan to model OMPL wall-clock cost
    Collision-recovery replans in simulation are instantaneous; in deployment they consume
    0.035–0.984 s of real time. replan_block_s converts that cost into a tick-level freeze so
    the policy is trained against realistic timing. Also clears the subgoal queue on recovery
    so agents plan directly to the final goal rather than retrying an already-contested subgoal,
    and removes the redundant ValidStateSamplerAllocator call from OMPL space-information setup.
